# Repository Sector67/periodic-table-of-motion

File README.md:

# Periodic Table of Motion

## Overview

A science museum needs interactive exhibits, and this is an exhibit that can easily be extended, is easy to setup and install, is robust and safe and easy to maintain. Exhibits can easily cost tens of thousands of dollars, but this one can grow to any size budget but the top of the line is still under $4k. The idea is a periodic table of motion, where each cell, instead of an element, is a type of mechanical motion. Inside the cell is a description of the motion, a button to activate it, and an actual example of a working machine that uses the principle. Simple machines (lever, pulley, gear, etc.) are at the top of each column, and they increase in complexity. For an example of the variety of types of motions I want to capture and show off, see http://507movements.com. This project is very educational and interactive, and distills the basics of mechanics into individual and easy to understand concepts, building on them to show advanced motion and power transfer in a fun way.

## Structure

A cell is the basic independent unit. It has a title, description, machine class, and example use. It also has a physical manifestation which is described with 3D cad files and a bill of materials and build instructions. It also has code to control the display, written in Arduino for an ATTiny.

The repository has a section for cells, which are all based on the template cell. Each subfolder in the cells subfolder is used for a different cell. The template_cell can be copied and extended.

The underlying electronics and enclosure for a cell is defined in the cell subfolder. These instructions are used to build every cell. The cells folder is how to modify that cell to be unique.

The table is the large structure that contains the cells. This can be modified to suit the installation, but the repository contains a sample wall that is 5 cells tall, 12 wide, and contains all the parts necessary for the power supply as well.

The power supply is an ATX computer supply. Sufficiently large installations should use multiple supplies, possibly one for every 3-4 columns, as a typical behavior might be for kids to push all the buttons at once.

## Current Status

As of 2015/08/17, the template is complete. Electronics are done and verified, example sketches exist for each piece of hardware, the structure for the project is defined and template documents exist to enable individual cells to be created. A sample cell has been created to verify everything.

Still to do is designing each of the individual cells, building and assembling them, and raising the funds to produce more than a few cells. However, the template cell proves that it's all do-able. Designing the individual cells will take the longest; assembling won't be too bad.

## Cost

A rough estimate of the cost of this project is as follows:

Wall mount:
 * Power supplies 5 ATX: $100
 * Wood/Plastic $200
 * Cables $100

Cells x60:
 * Polycarb $5
 * Enclosure materials $10
 * Electronics $10
 * Motors/Servos $15
 * Plastic printed/machined parts $10
 * LED strip $5

So $4-500 for the main part and $55 per cell.

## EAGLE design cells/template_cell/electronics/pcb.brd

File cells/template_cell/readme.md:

- Cell Title: {{name}}
- Machine Type: {{(one of) Lever, Wheel&Axle, Inclined Plane, Wedge, Screw, Pulley}}
- Description: {{short paragraph on what the machine does}}
- Used in: {{common uses}}

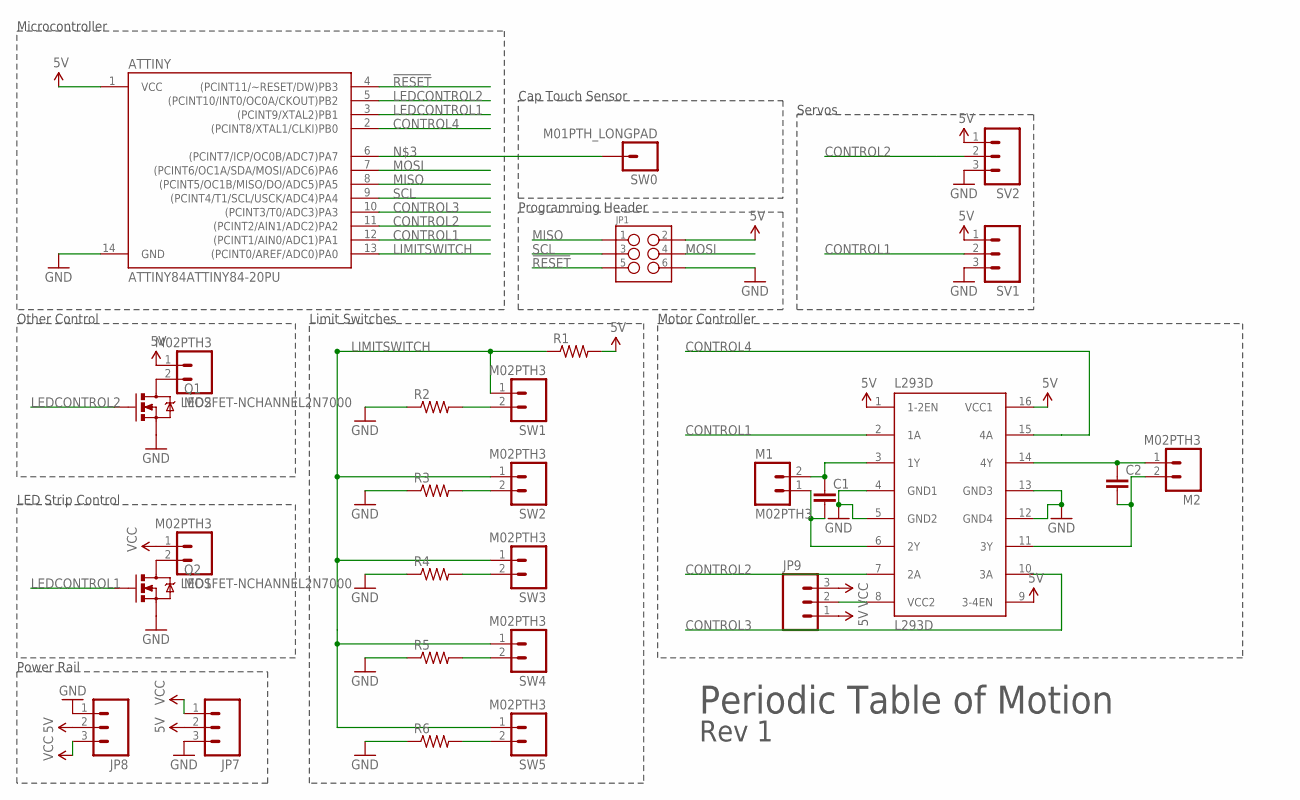
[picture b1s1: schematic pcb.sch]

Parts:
ATTINY: ATTINY84ATTINY84-20PU; DIL14
C1, C2: CAPPTH; CAP-PTH-SMALL
JP1: M03X22X3_SILK_MALE_PTH; 2X3
JP7, JP8: M03SCREW; SCREWTERMINAL-3.5MM-3
JP9: M03LONGPADS; 1X03_LONGPADS
L293D: L293D; DIL16
LED1, LED2: M02PTH3; 1X02_LONGPADS
M1, M2: M02PTH3; 1X02_LONGPADS
Q1, Q2: MOSFET-NCHANNEL2N7000; TO-92
R1, R2, R3, R4, R5, R6: RESISTORPTH-1/4W; AXIAL-0.4
SV1, SV2: M03LONGPADS; 1X03_LONGPADS
SW0: M01PTH_LONGPAD; 1X01_LONGPAD
SW1, SW2, SW3, SW4, SW5: M02PTH3; 1X02_LONGPADS

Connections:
5V: ATTINY.1 (VCC), JP1.2, JP7.2, JP8.2, JP9.1, L293D.1 (1-2EN), L293D.9 (3-4EN), L293D.16 (VCC1), LED2.1, R1.P$2 (2), SV1.1, SV2.1
!RESET: ATTINY.4 ((PCINT11/~RESET/DW)PB3), JP1.5
CONTROL1: ATTINY.12 ((PCINT1/AIN0/ADC1)PA1), L293D.2 (1A), SV1.2
CONTROL2: ATTINY.11 ((PCINT2/AIN1/ADC2)PA2), L293D.7 (2A), SV2.2
CONTROL3: ATTINY.10 ((PCINT3/T0/ADC3)PA3), L293D.10 (3A)
CONTROL4: ATTINY.2 ((PCINT8/XTAL1/CLKI)PB0), L293D.15 (4A)
GND: ATTINY.14 (GND), JP1.6, JP7.3, JP8.1, L293D.4 (GND1), L293D.5 (GND2), L293D.12 (GND4), L293D.13 (GND3), Q1.1 (S), Q2.1 (S), R2.P$1 (1), R3.P$1 (1), R4.P$1 (1), R5.P$1 (1), R6.P$1 (1), SV1.3, SV2.3
LEDCONTROL1: ATTINY.3 ((PCINT9/XTAL2)PB1), Q2.2 (G)
LEDCONTROL2: ATTINY.5 ((PCINT10/INT0/OC0A/CKOUT)PB2), Q1.2 (G)
LIMITSWITCH: ATTINY.13 ((PCINT0/AREF/ADC0)PA0), R1.P$1 (1), SW1.1, SW2.1, SW3.1, SW4.1, SW5.1
MISO: ATTINY.8 ((PCINT5/OC1B/MISO/DO/ADC5)PA5), JP1.1
MOSI: ATTINY.7 ((PCINT6/OC1A/SDA/MOSI/ADC6)PA6), JP1.4
unnamed: C2.1, L293D.14 (4Y), M2.1
unnamed: ATTINY.6 ((PCINT7/ICP/OC0B/ADC7)PA7), SW0.1
unnamed: C2.2, L293D.11 (3Y), M2.2
unnamed: C1.1, L293D.3 (1Y), M1.2
unnamed: C1.2, L293D.6 (2Y), M1.1
unnamed: R2.P$2 (2), SW1.2
unnamed: R3.P$2 (2), SW2.2
unnamed: JP9.2, L293D.8 (VCC2)
unnamed: LED1.2, Q2.3 (D)
unnamed: LED2.2, Q1.3 (D)
unnamed: R4.P$2 (2), SW3.2
unnamed: R5.P$2 (2), SW4.2
unnamed: R6.P$2 (2), SW5.2
SCL: ATTINY.9 ((PCINT4/T1/SCL/USCK/ADC4)PA4), JP1.3
VCC: JP7.1, JP8.3, JP9.3, LED1.1

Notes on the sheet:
Servos
Microcontroller
Power Rail
Motor Controller
Programming Header
LED Strip Control
Other Control
Limit Switches
Cap Touch Sensor
Periodic Table of Motion
Rev 1

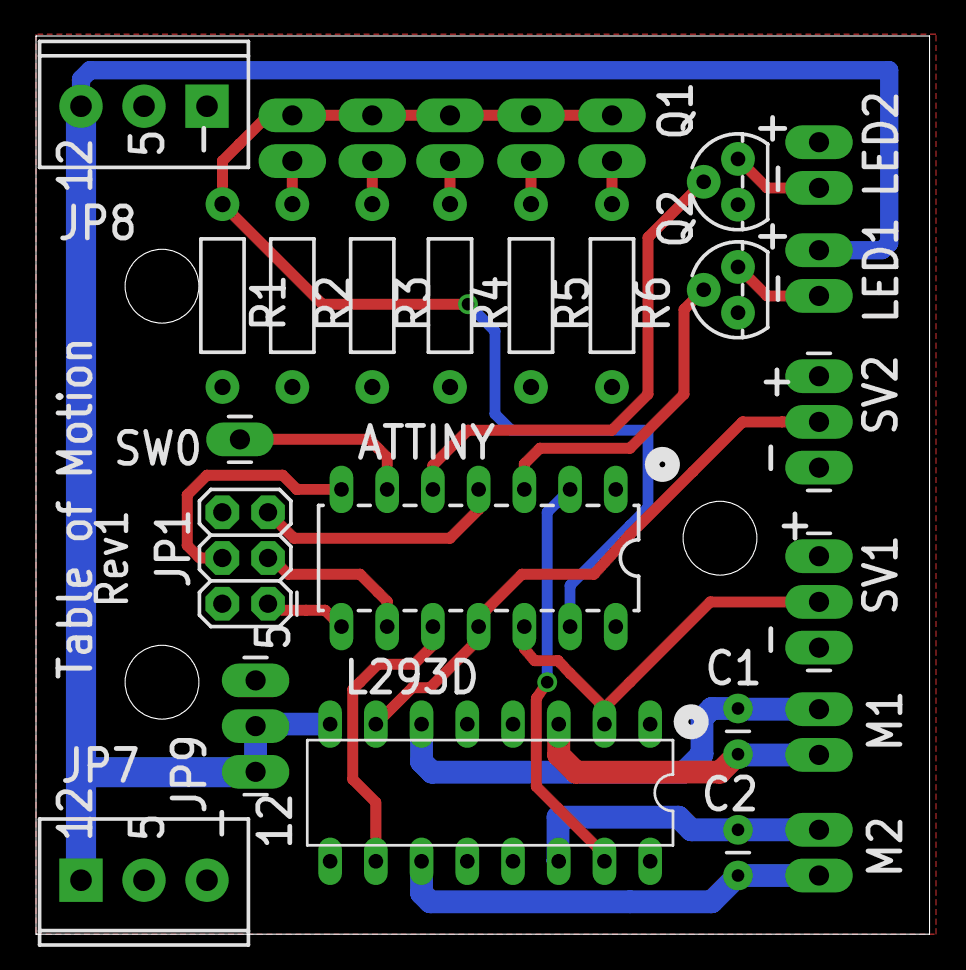
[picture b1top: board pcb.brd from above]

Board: 2 copper layers, 49.6 x 49.9 mm, 28 parts (0 on the bottom side), 27 nets.

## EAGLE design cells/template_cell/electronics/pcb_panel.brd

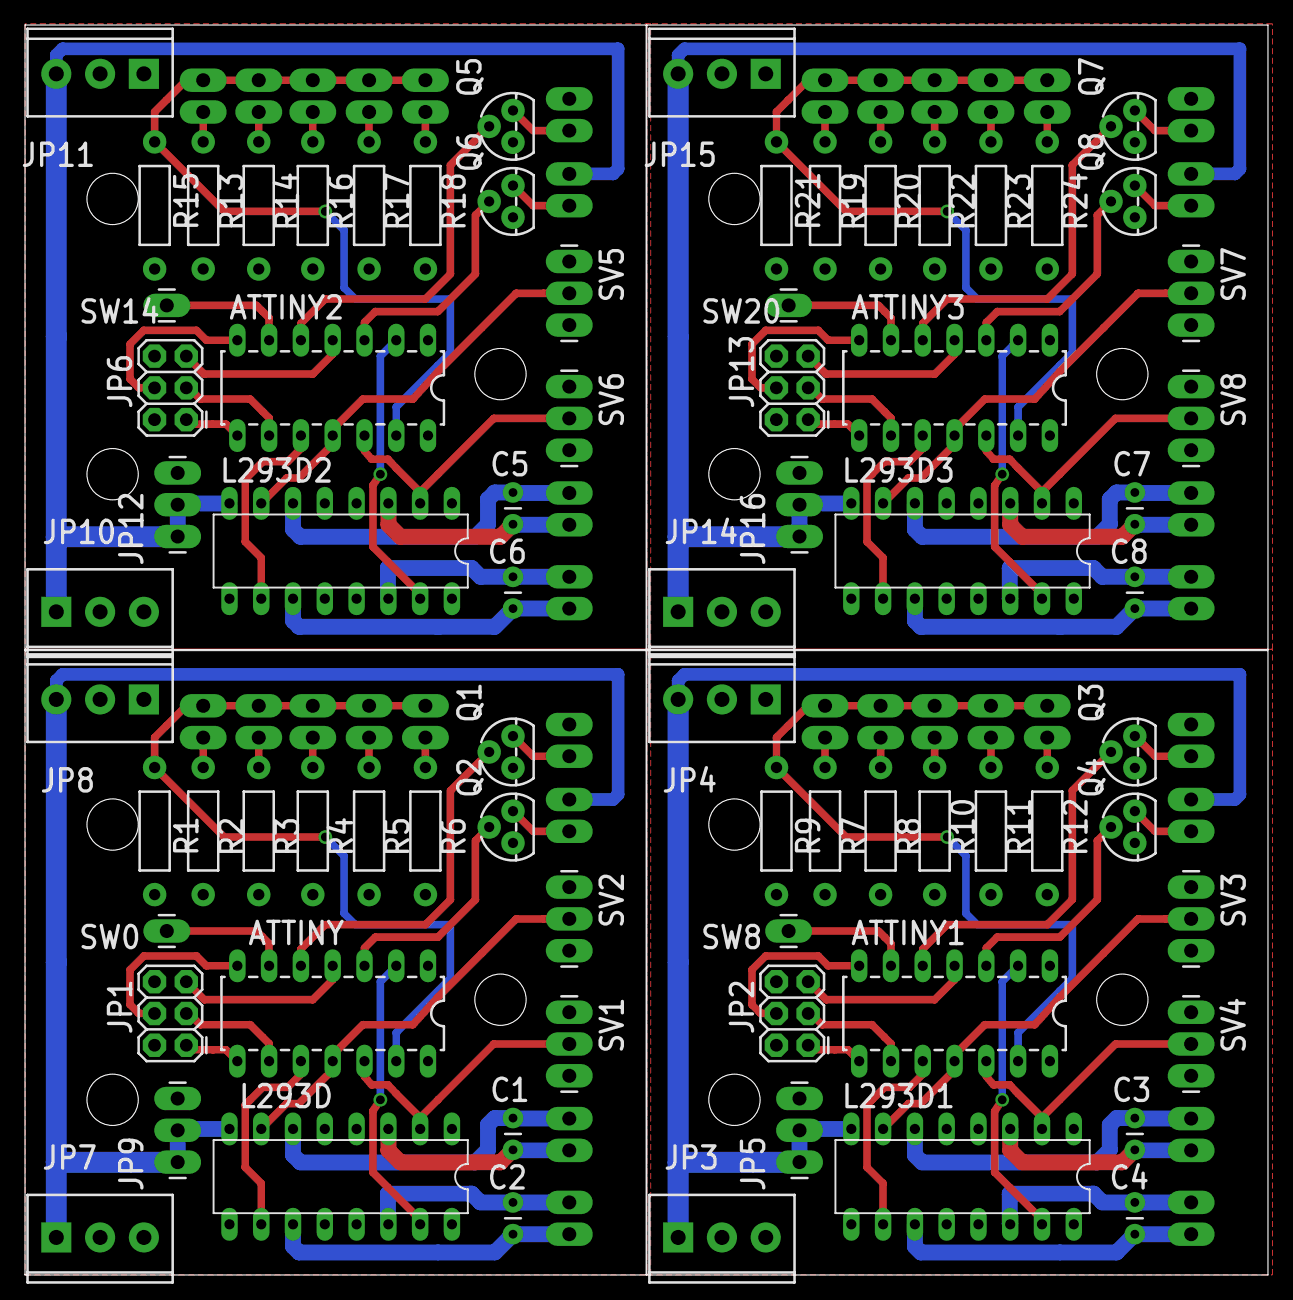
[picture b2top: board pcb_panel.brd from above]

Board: 2 copper layers, 99.3 x 99.9 mm, 112 parts (0 on the bottom side), 108 nets.

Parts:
ATTINY, ATTINY1, ATTINY2, ATTINY3: ATTINY84ATTINY84-20PU; DIL14
C1, C2, C3, C4, C5, C6, C7, C8: CAP-PTH-SMALL
JP1, JP2, JP6, JP13: 2X3
JP3, JP4, JP7, JP8, JP10, JP11, JP14, JP15: SCREWTERMINAL-3.5MM-3
JP5, JP9, JP12, JP16: 1X03_LONGPADS
L293D, L293D1, L293D2, L293D3: L293D; DIL16
LED1, LED2, LED3, LED4, LED5, LED6, LED7, LED8: M02PTH3; 1X02_LONGPADS
M1, M2, M3, M4, M5, M6, M7, M8: M02PTH3; 1X02_LONGPADS
Q1, Q2, Q3, Q4, Q5, Q6, Q7, Q8: MOSFET-NCHANNEL2N7000; TO-92
R1, R2, R3, R4, R5, R6, R7, R8, R9, R10, R11, R12, R13, R14, R15, R16, R17, R18, R19, R20, R21, R22, R23, R24: AXIAL-0.4
SV1, SV2, SV3, SV4, SV5, SV6, SV7, SV8: 1X03_LONGPADS
SW0, SW8, SW14, SW20: M01PTH_LONGPAD; 1X01_LONGPAD
SW1, SW2, SW3, SW4, SW5, SW6, SW7, SW9, SW10, SW11, SW12, SW13, SW15, SW16, SW17, SW18, SW19, SW21, SW22, SW23: M02PTH3; 1X02_LONGPADS

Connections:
5V: ATTINY.1, JP1.2, JP7.2, JP8.2, JP9.1, L293D.1, L293D.9, L293D.16, LED2.1, R1.P$2, SV1.1, SV2.1
5V1: ATTINY1.1, JP2.2, JP3.2, JP4.2, JP5.1, L293D1.1, L293D1.9, L293D1.16, LED4.1, R9.P$2, SV3.1, SV4.1
5V2: ATTINY2.1, JP6.2, JP10.2, JP11.2, JP12.1, L293D2.1, L293D2.9, L293D2.16, LED6.1, R15.P$2, SV5.1, SV6.1
5V3: ATTINY3.1, JP13.2, JP14.2, JP15.2, JP16.1, L293D3.1, L293D3.9, L293D3.16, LED8.1, R21.P$2, SV7.1, SV8.1
!RESET: ATTINY.4, JP1.5
!RESET1: ATTINY1.4, JP2.5
!RESET2: ATTINY2.4, JP6.5
!RESET3: ATTINY3.4, JP13.5
CONTROL1: ATTINY.12, L293D.2, SV1.2
CONTROL2: ATTINY.11, L293D.7, SV2.2
CONTROL3: ATTINY.10, L293D.10
CONTROL4: ATTINY.2, L293D.15
CONTROL5: ATTINY1.12, L293D1.2, SV4.2
CONTROL6: ATTINY1.11, L293D1.7, SV3.2
CONTROL7: ATTINY1.2, L293D1.15
CONTROL8: ATTINY1.10, L293D1.10
CONTROL9: ATTINY2.12, L293D2.2, SV6.2
CONTROL10: ATTINY2.11, L293D2.7, SV5.2
CONTROL11: ATTINY2.2, L293D2.15
CONTROL12: ATTINY2.10, L293D2.10
CONTROL13: ATTINY3.12, L293D3.2, SV8.2
CONTROL14: ATTINY3.11, L293D3.7, SV7.2
CONTROL15: ATTINY3.2, L293D3.15
CONTROL16: ATTINY3.10, L293D3.10
GND: ATTINY.14, JP1.6, JP7.3, JP8.1, L293D.4, L293D.5, L293D.12, L293D.13, Q1.1, Q2.1, R2.P$1, R3.P$1, R4.P$1, R5.P$1, R6.P$1, SV1.3, SV2.3
GND1: ATTINY1.14, JP2.6, JP3.3, JP4.1, L293D1.4, L293D1.5, L293D1.12, L293D1.13, Q3.1, Q4.1, R7.P$1, R8.P$1, R10.P$1, R11.P$1, R12.P$1, SV3.3, SV4.3
GND2: ATTINY2.14, JP6.6, JP10.3, JP11.1, L293D2.4, L293D2.5, L293D2.12, L293D2.13, Q5.1, Q6.1, R13.P$1, R14.P$1, R16.P$1, R17.P$1, R18.P$1, SV5.3, SV6.3
GND3: ATTINY3.14, JP13.6, JP14.3, JP15.1, L293D3.4, L293D3.5, L293D3.12, L293D3.13, Q7.1, Q8.1, R19.P$1, R20.P$1, R22.P$1, R23.P$1, R24.P$1, SV7.3, SV8.3
LEDCONTROL1: ATTINY.3, Q2.2
LEDCONTROL2: ATTINY.5, Q1.2
LEDCONTROL3: ATTINY1.3, Q4.2
LEDCONTROL4: ATTINY1.5, Q3.2
LEDCONTROL5: ATTINY2.3, Q6.2
LEDCONTROL6: ATTINY2.5, Q5.2
LEDCONTROL7: ATTINY3.3, Q8.2
LEDCONTROL8: ATTINY3.5, Q7.2
LIMITSWITCH: ATTINY.13, R1.P$1, SW1.1, SW2.1, SW3.1, SW4.1, SW5.1
LIMITSWITCH1: ATTINY1.13, R9.P$1, SW6.1, SW7.1, SW9.1, SW10.1, SW11.1
LIMITSWITCH2: ATTINY2.13, R15.P$1, SW12.1, SW13.1, SW15.1, SW16.1, SW17.1
LIMITSWITCH3: ATTINY3.13, R21.P$1, SW18.1, SW19.1, SW21.1, SW22.1, SW23.1
MISO: ATTINY.8, JP1.1
MISO1: ATTINY1.8, JP2.1
MISO2: ATTINY2.8, JP6.1
MISO3: ATTINY3.8, JP13.1
MOSI: ATTINY.7, JP1.4
MOSI1: ATTINY1.7, JP2.4
MOSI2: ATTINY2.7, JP6.4
MOSI3: ATTINY3.7, JP13.4
unnamed: C2.1, L293D.14, M2.1
unnamed: ATTINY.6, SW0.1
unnamed: C4.1, L293D1.14, M3.1
unnamed: C2.2, L293D.11, M2.2
unnamed: C1.1, L293D.3, M1.2
unnamed: C1.2, L293D.6, M1.1
unnamed: C4.2, L293D1.11, M3.2
unnamed: C3.1, L293D1.3, M4.2
unnamed: C3.2, L293D1.6, M4.1
unnamed: R7.P$2, SW6.2
unnamed: R2.P$2, SW1.2
unnamed: R3.P$2, SW2.2
unnamed: R8.P$2, SW7.2
unnamed: ATTINY1.6, SW8.1
unnamed: LED3.2, Q4.3
unnamed: JP9.2, L293D.8
unnamed: LED1.2, Q2.3
unnamed: LED2.2, Q1.3
unnamed: LED4.2, Q3.3
unnamed: R10.P$2, SW9.2
unnamed: R4.P$2, SW3.2
unnamed: R11.P$2, SW10.2
unnamed: R5.P$2, SW4.2
unnamed: R12.P$2, SW11.2
unnamed: R6.P$2, SW5.2
unnamed: JP5.2, L293D1.8
unnamed: C6.1, L293D2.14, M5.1
unnamed: C6.2, L293D2.11, M5.2
unnamed: C5.1, L293D2.3, M6.2
unnamed: C5.2, L293D2.6, M6.1
unnamed: R13.P$2, SW12.2
unnamed: R14.P$2, SW13.2
unnamed: ATTINY2.6, SW14.1
unnamed: LED5.2, Q6.3
unnamed: LED6.2, Q5.3
unnamed: R16.P$2, SW15.2
unnamed: R17.P$2, SW16.2
unnamed: R18.P$2, SW17.2
unnamed: JP12.2, L293D2.8
unnamed: C8.1, L293D3.14, M7.1
unnamed: C8.2, L293D3.11, M7.2
unnamed: C7.1, L293D3.3, M8.2
unnamed: C7.2, L293D3.6, M8.1
unnamed: R19.P$2, SW18.2
unnamed: R20.P$2, SW19.2
unnamed: ATTINY3.6, SW20.1
unnamed: LED7.2, Q8.3
unnamed: LED8.2, Q7.3
unnamed: R22.P$2, SW21.2
unnamed: R23.P$2, SW22.2
unnamed: R24.P$2, SW23.2
unnamed: JP16.2, L293D3.8
SCL: ATTINY.9, JP1.3
SCL1: ATTINY1.9, JP2.3
SCL2: ATTINY2.9, JP6.3
SCL3: ATTINY3.9, JP13.3
VCC: JP7.1, JP8.3, JP9.3, LED1.1
VCC1: JP3.1, JP4.3, JP5.3, LED3.1
VCC2: JP10.1, JP11.3, JP12.3, LED5.1
VCC3: JP14.1, JP15.3, JP16.3, LED7.1

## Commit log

2015-07-08 Initial commit
    Initial commit of cell, wall, and cell template.
2015-07-09 Rename readme.txt to readme.md
2015-07-09 Tweak for markdown
2015-07-09 Rename description.md to readme.md
    so that it shows up underneath the file browser on Github
2015-07-09 Add a file describing how to add new boxes
2015-07-09 Relaying out the board
    laying out the board again for production, easier to read, components
    aligned and placed better. ready for first rev production
2015-10-16 Moving electronics folder to template_cell
    template_cell folder should contain all the things necessary to make a
    cell, including the generic things like the electronics and basic
    reusable parts.
2015-10-16 Adding template cell enclosure and basic parts
2015-10-16 Adding Archimedes Screw cell
2015-10-16 Adding Axial Cam Follower cell
2015-10-16 Adding Bevel Gear cell
2015-10-16 Adding Crazy Gear cell
    Unfortunately, I don't have the design files for the original gears.
    These parts are just supplemental parts that allowed me to attach to the
    gear.
2015-10-16 Adding Gear Ratio cell
    There are actually two cells here. One has a big to little ratio and the
    other is little to big.
2015-10-16 Adding Radial Cam Follower cell
2015-10-16 Adding Ratchet Cell
2015-10-16 Adding Wedge Cell
2015-10-16 Adding Wheel and Axle cell
2015-11-08 Redoing the bevel gear to have a bushing
2015-11-08 Lever descriptions
2016-02-02 Adding firmware and readme text

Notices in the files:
parts and their libraries:
SparkFun-DigitalIC: Licensing: Creative Commons ShareAlike 4.0 International - https://creativecommons.org/licenses/by-sa/4.0
